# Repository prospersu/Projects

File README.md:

# Projects

This section outlines key hardware and software projects completed during my bachelor's degree studies.

---

## SDR 2.0: Low-Cost WSPR Receiver Design 

* Designed and simulated the analog signal chain for a Software Defined Radio (SDR) receiver targeting the 7.04MHz WSPR (Weak Signal Propagation Reporter) band.
* Engineered the **Tayloe detector (mixer)** stage to successfully down-convert the 7.0401 MHz carrier frequency to the 1.4 kHz - 1.6 kHz audio range required for digital processing.
* Redesigned the **audio amplifier** stage using an active low-pass filter configuration to boost the output voltage (from 0.7V) to meet the input requirements of the selected ADC.
* Performed **overall circuit simulation using LTspice**, validating that the analog front-end achieved the target frequency range and an output level of 0.957 Vrms.
* Contributed to the 4-layer PCB design by creating the **schematic capture and layout** for the mixer and audio amplifier sections using **KiCAD**.

---

## Water Quality Monitoring Solution with Community Engagement 

* Contributed to a proposed solution for the Illawarra Local Aboriginal Land Council (ILALC) to monitor creek water quality using a three-tiered approach: hardware (data loggers), software (app/visualization), and community engagement (tours).
* Involved in the **hardware design concept**, including the selection of professional-grade sensors (**HOBO MX2001** for water level, **HOBO MX2501** for pH/temp) and the **CAD design** of a buoyant, waterproof acrylic casing to house them.
* Conducted a **hardware feasibility study** using Newtonian mechanics and fluid dynamics to analyze the forces (drag, buoyancy, friction) acting on the submerged data logger and its cement block anchor, determining optimal dimensions (0.095m x 0.095m x 0.762m block) for stability in worst-case flow conditions (2.5 m/s).
* Assisted in defining the system architecture for data transmission from sensors via **Bluetooth/Internet** to a private cloud database and subsequent visualization using **Python (Pandas/Matplotlib)**.

---

## Microsoft & USYD Digital Campus Transformation Project 

* Provided **key engineering analysis** within a 6-person team (Synergy Squad) evaluating the feasibility and implementation limitations of advanced AI technologies (like Microsoft Copilot) for the University of Sydney's digital campus transformation.
* Applied **design thinking methodologies** to identify stakeholder (students, staff) pain points related to AI adoption, infrastructure limitations, and the need for flexible learning.
* Co-developed potential solutions integrating AI tools, such as proposing a **Copilot-driven summarization bot** to help students catch up on missed content and recommending an **"opt-out" policy** for AI usage to foster autonomy.
* Contributed engineering perspectives to the final strategy report advising the university on navigating digital transformation, AI integration, and evolving learning trends.

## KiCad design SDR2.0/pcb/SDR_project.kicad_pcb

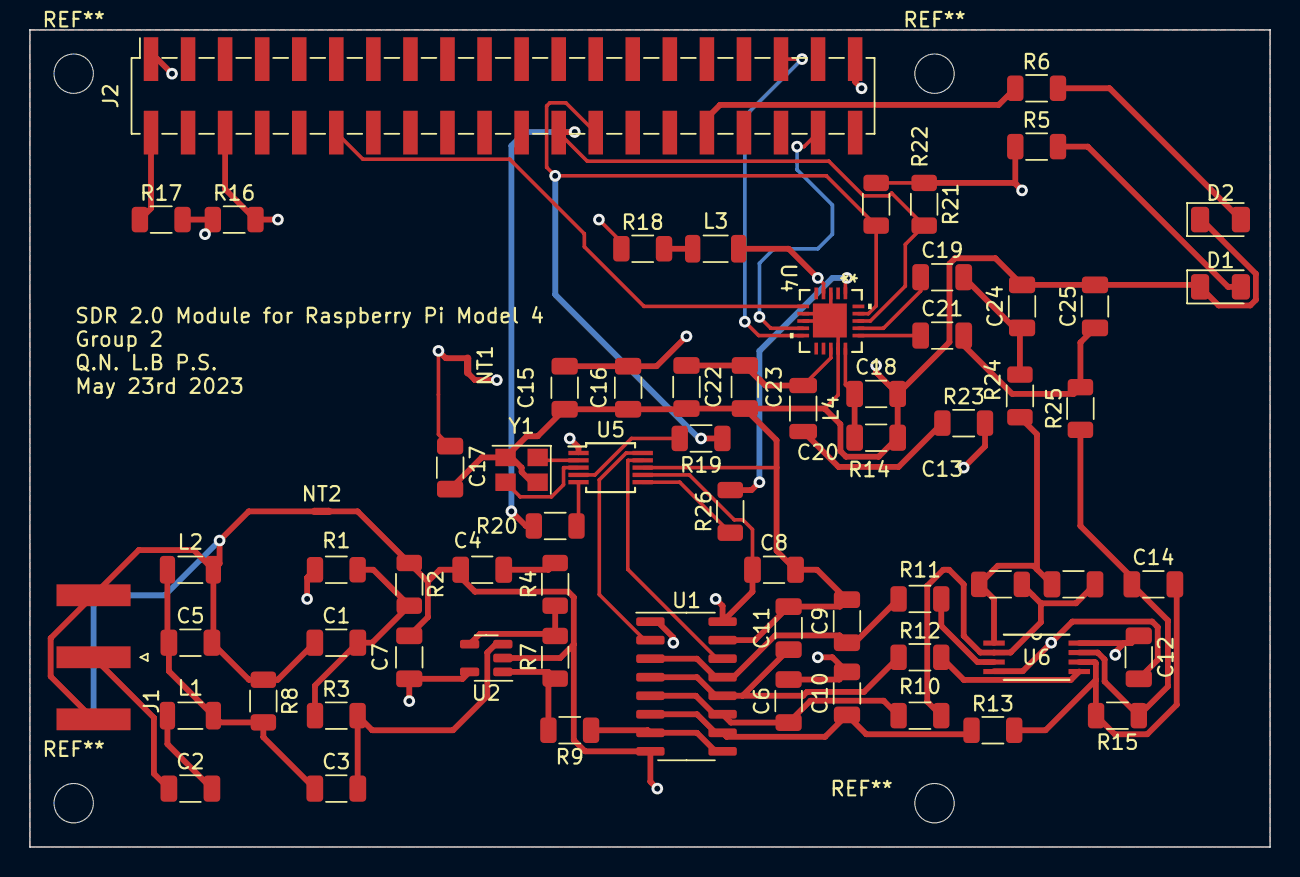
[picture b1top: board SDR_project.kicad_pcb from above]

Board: 4 copper layers, 85.0 x 56.0 mm, 67 parts (0 on the bottom side), 49 nets.

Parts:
C1, C3: 0.01uF; C_1206_3216Metric
C2: 8.87pF; C_1206_3216Metric
C4, C6, C7, C8, C9, C10, C11, C12, C16, C17, C18, C23: 0.1uF; C_1206_3216Metric
C5: 23.2nF; C_1206_3216Metric
C13, C14: 3300pF; C_1206_3216Metric
C15, C22: 10uF; C_1206_3216Metric
C19, C21: 1uF; C_1206_3216Metric
C20: 4.7uF; C_1206_3216Metric
C24, C25: 220pF; C_1206_3216Metric
D1: LED yellow; D_1206_3216Metric
D2: LED blue; D_1206_3216Metric
J1: Conn_Coaxial; SMA_Amphenol_132289_EdgeMount
J2: Conn_02x20_Odd_Even; PinSocket_2x20_P2.54mm_Vertical_SMD
L1: 57.6uH; L_1206_3216Metric
L2: 22.1nH; L_1206_3216Metric
L3, L4: 47uH, 15mA; L_1206_3216Metric
NT1, NT2: NetTie_2; NetTie-2_SMD_Pad0.5mm
R1, R2, R3: 470; R_1206_3216Metric
R4: 47; R_1206_3216Metric
R5: 62; R_1206_3216Metric
R6: 200; R_1206_3216Metric
R7, R18, R23: 220; R_1206_3216Metric
R8, R10, R11, R12, R13: 50; R_1206_3216Metric
R9: 100; R_1206_3216Metric
R14, R15: 30K; R_1206_3216Metric
R16: 20k; R_1206_3216Metric
R17: 10k; R_1206_3216Metric
R19, R20, R26: 30; R_1206_3216Metric
R21, R22: 2.43k; R_1206_3216Metric
R24, R25: 5.6k; R_1206_3216Metric
U1: TS3A5017; SOIC-16_3.9x9.9mm_P1.27mm
U2: THS4304; SOT-23-5
U4: SSM2604CPZ-REEL7; CP_20_4_ADI
U5: Si5351A-B-GT; MSOP-10_3x3mm_P0.5mm
U6: TL972IPWR; PW8
Y1: Crystal; Crystal_SMD_TXC_7M-4Pin_3.2x2.5mm

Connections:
3.3V PIN 1: C17.1, J2.1, NT1.1, R18.1
5V to 3.3V PIN2: C7.2, C8.1, C12.1, NT1.2, R1.2, R5.1, R16.1, R17.2, R21.1, R22.1, R23.2, U1.16 (VCC), U2.5 (V+), U5.1 (VDD), U5.7 (VDDO), U6.8 (VCC+)
CLK0: U1.2 (IN2), U5.10 (CLK0)
CLK0 Phase 90: U1.14 (IN1), U5.9 (CLK1)
CLK2 ADC: R26.2, U4.1 (MCLK/XTI)
GND: C1.1, C5.2, J1.2 (Ext), J2.6, L2.2, NT2.1, R8.1, R16.2
GNDREF: C4.1, C6.2, C7.1, C8.2, C9.2, C10.2, C11.2, C12.2, C15.2, C16.1, C17.2, C18.2, C20.2, C22.2, C23.1, C24.2, C25.2, D1.1 (K), D2.1 (K), J2.39, NT2.2, R2.1, U1.1 (1EN), U1.8 (GND), U1.15 (2EN), U2.2 (V-), U4.3 (DGND), U4.7 (PBDAT), U4.8 (PBLRC), U4.14 (AGND), U4.21 (GND), U5.8 (GND), U6.4 (VCC-), Y1.2, Y1.4
I+: C6.1, R10.2, U1.5 (1S2), U1.11 (2S2)
I-: C9.1, R11.2, U1.3 (1S4), U1.13 (2S4)
LED_IN: J2.32, R6.1
LINE IN I: C13.1, R14.1, R24.1, U6.1 (OUT1)
LINE IN Q: C14.1, R15.1, R25.1, U6.7 (OUT2)
unnamed: C1.2, R1.1, R2.2, R3.1
unnamed: C2.2, L1.1
unnamed: C4.2, R4.2
unnamed: C19.2, C24.1, R24.2
unnamed: C21.2, C25.1, R25.2
unnamed: D1.2 (A), R5.2
unnamed: D2.2 (A), R6.2
unnamed: C2.1, J1.1 (In)
unnamed: J2.2, R17.1
unnamed: L3.1, R18.2
unnamed: L4.2, R23.1
unnamed: C3.2, R3.2, U2.3 (+)
unnamed: R4.1, R7.2, U2.4 (-)
unnamed: R7.1, R9.2, U2.1 (VOUT)
unnamed: C22.1, C23.2, L4.1, U4.13 (AVDD)
unnamed: C15.1, C16.2, L3.2, U4.4 (DVDD)
unnamed: C19.1, U4.17 (LLINEIN)
unnamed: C21.1, U4.16 (RLINEIN)
unnamed: C18.1, C20.1, U4.15 (VMID)
unnamed: R26.1, U5.6 (CLK2)
unnamed: R19.2, U5.4 (SCL)
unnamed: R20.2, U5.5 (SDA)
unnamed: U5.2 (XA), Y1.1
unnamed: U5.3 (XB), Y1.3
unnamed: R11.1, U6.3 (IN1+)
unnamed: C13.2, R10.1, R14.2, U6.2 (IN1-)
unnamed: R12.2, U6.5 (IN2+)
unnamed: C14.2, R13.2, R15.2, U6.6 (IN2-)
PCM_CLK PIN 12: J2.12, U4.6 (BCLK)
PCM_DIN PIN 38: J2.38, U4.9 (RECDAT)
PCM_FS PIN 35: J2.35, U4.10 (RECLRC)
Q+: C10.1, R13.1, U1.6 (1S1), U1.10 (2S1)
Q-: C11.1, R12.1, U1.4 (1S3), U1.12 (2S3)
RF 7MHz: C3.1, C5.1, L1.2, L2.1, R8.2
RFOUT: R9.1, U1.7 (1D), U1.9 (2D)
SCL4 PIN26: J2.26, R19.1, R22.2, U4.19 (SCLK)
SDA4 PIN24: J2.24, R20.1, R21.2, U4.18 (SDIN)

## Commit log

2025-10-18 Create temp
